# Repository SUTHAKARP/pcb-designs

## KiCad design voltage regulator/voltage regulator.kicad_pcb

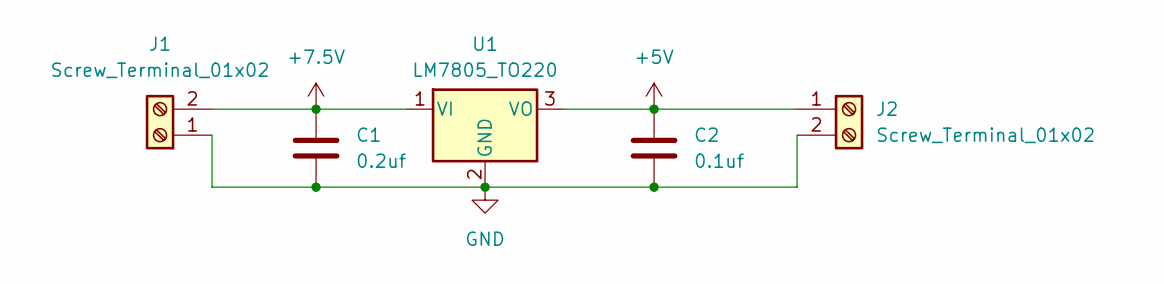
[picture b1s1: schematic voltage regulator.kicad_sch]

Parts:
C1: 0.2uf; C_1206_3216Metric_Pad1.33x1.80mm_HandSolder
C2: 0.1uf; C_1206_3216Metric_Pad1.33x1.80mm_HandSolder
J1, J2: Screw_Terminal_01x02; TerminalBlock_Phoenix_MKDS-1,5-2_1x02_P5.00mm_Horizontal
U1: LM7805_TO220; TO-220-3_Vertical

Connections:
+5V: C2.1, J2.1, U1.3 (VO)
+7.5V: C1.1, J1.2, U1.1 (VI)
GND: C1.2, C2.2, J1.1, J2.2, U1.2 (GND)

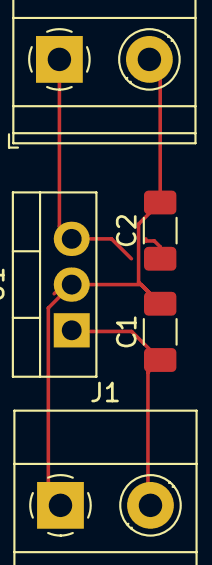
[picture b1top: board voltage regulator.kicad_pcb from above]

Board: 2 copper layers, 5 parts (0 on the bottom side), 3 nets.
